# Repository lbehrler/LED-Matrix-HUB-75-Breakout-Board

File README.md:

# LED-Matrix-HUB-75-Breakout-Board
KiCAD files for LED Matrix HUB75 Breakout Board for ESP32

This is a work in progress for a simple ESP32 to HUB75 breakout board.   

_**Please use at your own risk**_

## Process so far:
1. Build and test breadboard prototype
2. Build and test perf board prototype
3. Develop KiCAD for intial prototype PCB Rev 0
4. Order and test prototype boards from PCB house Rev 0
5. Revise KiCAD model to Rev 1 (incorporating a fuse and power i/o changes)
6. NEXT STEP: Order and test Rev 1 prototype PCB   <<<<<<<< 
7. 

### Rev 0 board

### Rev 1 Renderings

##

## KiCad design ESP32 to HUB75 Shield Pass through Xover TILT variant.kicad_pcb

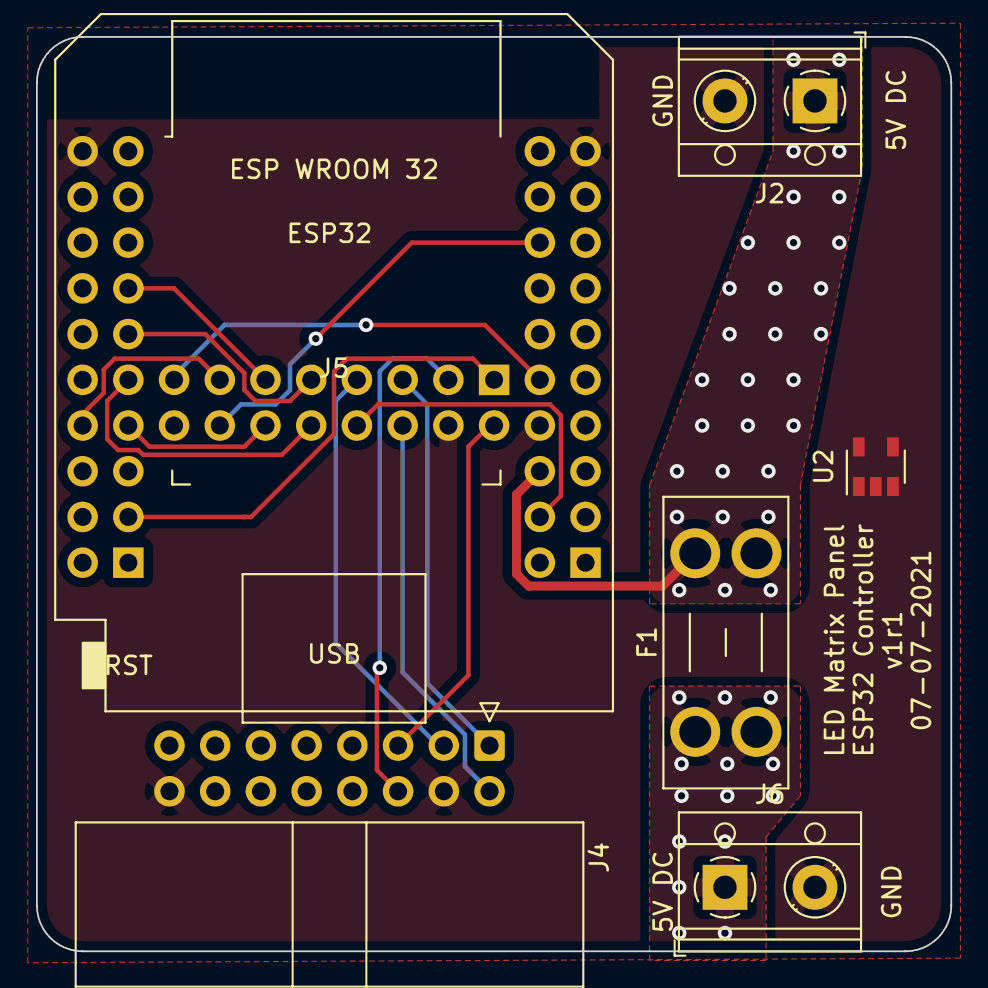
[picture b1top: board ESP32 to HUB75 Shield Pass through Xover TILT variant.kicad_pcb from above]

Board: 2 copper layers, 50.8 x 50.8 mm, 7 parts (1 on the bottom side), 17 nets.

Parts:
F1: Fuse; Fuseholder_Blade_Mini_Keystone_3568
J2: Pwr In; TerminalBlock_RND_205-00012_1x02_P5.00mm_Horizontal
J3: LED Matrix Pinheader; PinSocket_2x08_P2.54mm_Vertical
J4: LED X-over Data Out Socket; IDC-Header_2x08_P2.54mm_Horizontal
J5: Pin-Socket-02x10x02_ESP32-Mini-ESP32_mini; ESP32_mini-MHET-Live
J6: Pwr Out to LED Matrix; TerminalBlock_RND_205-00012_1x02_P5.00mm_Horizontal
U2: LP2985-3.3; SOT-23-5

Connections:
/B1: J3.3, J4.6
/B2: J3.7, J4.3
/G1: J3.2, J4.5
/G2: J3.6, J4.2
/R2: J3.5, J4.1
GND: J2.2, J3.4, J3.16, J4.4, J4.16, J5.a1, J5.c7, J5.d1, J6.2
IO5: J3.12, J5.b7
IO13: J3.1, J5.b9
IO14: J3.13, J5.a7
IO15: J3.8, J5.c9
IO16: J3.15, J5.c6
IO18: J3.11, J5.b4
IO19: J3.9, J5.b5
IO22: J3.14, J5.c3
IO23: J3.10, J5.b6
VCC: F1.2, J2.1, J5.c8
VFZ: F1.1, J6.1

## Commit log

2021-07-20 Update LICENSE
2021-07-22 Added board renderings
2021-07-22 More photos
